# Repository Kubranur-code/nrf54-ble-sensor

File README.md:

# nRF54L10 BLE Sensor Board

A small Bluetooth Low Energy sensor board built around Nordic's nRF54L10. The chip is placed directly on the board, not used through a radio module. It runs from a single CR2032 coin cell, measures temperature, humidity and motion, and transmits through a PCB antenna I laid out myself. The board is 35 × 45 mm, has four layers and is designed in KiCad 9 for assembly at JLCPCB.

*Top side. The antenna is in the top-left corner, the nRF54L10 is in the middle and the coin-cell holder takes up the lower half. All parts are on this side.*

## Why I built this

Most hobby BLE boards use a pre-certified module. The module hides the hardest part of the design: the RF matching, the antenna and the ground around them. I wanted to do that part myself, so this board uses the bare QFN48 chip with Nordic's matching network and a printed inverted-F antenna. I added a small tuning network between them so the antenna can later be measured and adjusted with a VNA without a new board.

The second goal was low power. The board has no regulator and no power switch, and the accelerometer wakes the chip only when the board moves. A coin cell should therefore last a long time.

## Hardware overview

| | |
|---|---|
| SoC | nRF54L10-QFAA (Cortex-M33, 1 MB RRAM, 192 KB RAM, Bluetooth LE) |
| Sensors | Sensirion SHT40 (temperature/humidity), ST LIS2DH12 (accelerometer), shared I²C bus |
| Power | CR2032 straight to VDD, internal DC/DC converter, 47 µF buffer capacitor |
| Clocks | 32 MHz crystal, 32.768 kHz crystal |
| Antenna | Inverted-F PCB antenna (TI SWRA117D) after a 0 Ω + 2 × DNP π network |
| Debug | 10-pin 1.27 mm Cortex Debug connector (SWD + SWO), test pad for timing current measurements |
| User I/O | One button, one LED |
| PCB | 35 × 45 mm, 4 layers, JLC04161H-1080 stackup, ENIG, 2 × M2 mounting holes |

## Design notes

### Choosing the nRF54L10

I started with the nRF54L15, because there are already many open nRF52 designs and the nRF54L series is newer and uses less power. When I checked stock, JLCPCB had no L15, so I switched to the nRF54L10. It is pin compatible and has less memory, which this application does not need. I checked the schematic symbol pin by pin against both datasheets before changing the part.

### Running from a coin cell

The nRF54L works from 1.7 to 3.6 V, so a regulator between the cell and the chip would only add its own quiescent current. Instead, the chip's internal DC/DC converter is enabled with the 4.7 µH inductor from Nordic's reference design. A CR2032 has a high internal resistance and cannot deliver the radio's current peaks cleanly, so a 47 µF ceramic capacitor next to the holder covers them.

The LIS2DH12 stays in its low-power mode and its INT1 pin can wake the nRF54L10 from System OFF. The radio therefore only runs when something happens. Its address pin SA0 is tied to VDD, because the pin has an internal pull-up and tying it to ground would draw a small but constant current.

### Clocks

The chip can run its low-frequency clock from an internal RC oscillator, but that oscillator drifts with temperature. It has to be recalibrated regularly, which means starting the 32 MHz crystal, and its larger error forces wider BLE receive windows. Both cost more energy over time than a small 32.768 kHz crystal, so the board has one. Both crystals use the chip's internal load capacitors.

### RF path and antenna

The matching network between the ANT pin and the 50 Ω point is copied part for part from Nordic's QFAA reference layout, using the same Murata 0201 inductors and capacitors. I also kept the reference's ground return for the VSS_PA shunt capacitor: it goes back to the chip only on the top layer, not through a via. After the 50 Ω point comes a 0402 π network with a 0 Ω resistor and two unpopulated capacitor pads (C13, C14). These are the pads I will use to tune the antenna once I can measure it.

The SoC, the matching network and the antenna feed are placed on one straight line, so the RF trace from the ANT pin to the antenna has no bends. The antenna area is kept free of copper on all four layers, and a row of ground vias runs along the RF path.

### Stackup

I used JLCPCB's JLC04161H-1080 stackup. Its prepreg between the top layer and the first ground plane is only 0.076 mm thick. A thin dielectric keeps the ground close under the ANT pin, which Nordic recommends for suppressing harmonics. It also makes the 50 Ω line narrow enough for 0201 pads: as a grounded coplanar waveguide the line is 0.13 mm wide with 0.15 mm gaps.

| Layer | Use |
|---|---|
| L1 | Components, RF, most signals |
| L2 | Solid ground plane |
| L3 | VDD plane, one short signal |
| L4 | Ground pour, signals that change layer |

### Layout

The hardest part of the layout was the left side of the QFN. Its 0.4 mm pitch pins carry the button, the LED, both I²C lines, the accelerometer interrupt and the DC/DC loop. In the first placement the I²C pull-ups and the ferrite bead were directly in front of these pins, and there was no room to get the traces out. The autorouter failed here as well. Pull-ups work anywhere on the bus, so I moved them down next to the humidity sensor. The remaining traces that could not escape on the top layer change to the bottom layer through vias. The ground plane under all top-layer signals stays unbroken.

The DECRF pin needs a connection to DECA on the other side of the chip, and on the top layer that path is blocked by the crystal traces. I copied the solution from Nordic's layout: the DECRF capacitor sits right at the pin, and a via behind it carries the connection on the bottom layer to the DECA side.

The ground pours on L1 and L4 are stitched to the L2 plane with vias on a 2.5 mm grid, about λ/25 at 2.4 GHz. Two M2 mounting holes sit in opposite corners. The antenna corner has to stay free of metal and the coin-cell holder covers the fourth corner, so two diagonal holes were the practical choice. ERC and DRC, including schematic parity, finish with no violations. The reports are in `fab/`.

*Bottom side: ground pour, stitching vias and the few signals that use L4. The antenna keep-out appears top-right because the view is mirrored.*

## Project status

The design is finished, but the board has **not been manufactured yet**. Nothing in this repository has been tested on real hardware.

## Ordering from JLCPCB

1. Upload `fab/nrf54-ble-sensor-gerbers.zip`. Select 4 layers, 1.6 mm thickness, ENIG and impedance control with the JLC04161H-1080 stackup.
2. For assembly, upload `fab/nrf54-ble-sensor-bom.csv` and `fab/nrf54-ble-sensor-cpl.csv`. C13 and C14 are left out on purpose.
3. Check the part rotations in JLCPCB's placement preview before ordering. Their library sometimes uses a different orientation than KiCad, most often for QFN, LGA and crystal packages.

## Repository layout

```
nrf54-ble-sensor.kicad_*   KiCad 9 project
lib/                       symbols, footprints and 3D models not in the KiCad library
docs/                      schematic PDF and renders
fab/                       Gerbers, drill files, BOM, CPL, ERC/DRC reports
scripts/export.sh          regenerates everything in fab/ and docs/
```

All outputs are generated with `kicad-cli` by running `bash scripts/export.sh`. The 3D models of the two crystals and the SHT40 are from the LCSC/EasyEDA part library.

## References

- Nordic Semiconductor, nRF54L15/L10 product specification and QFAA reference layout v0.8
- Texas Instruments, SWRA117D, *2.4 GHz Inverted F Antenna*
- Nordic DevZone discussions on ANT pin ground distance and harmonics
- JLCPCB impedance-controlled stackups

## License

Copyright 2026 Kübranur Cici.

The hardware design files in this repository are licensed under the [CERN Open Hardware Licence Version 2 – Strongly Reciprocal](LICENSE) (CERN-OHL-S-2.0). The 3D models in `lib/parts.3dshapes` and the Nordic reference material referred to above belong to their respective owners and are not covered by this licence.

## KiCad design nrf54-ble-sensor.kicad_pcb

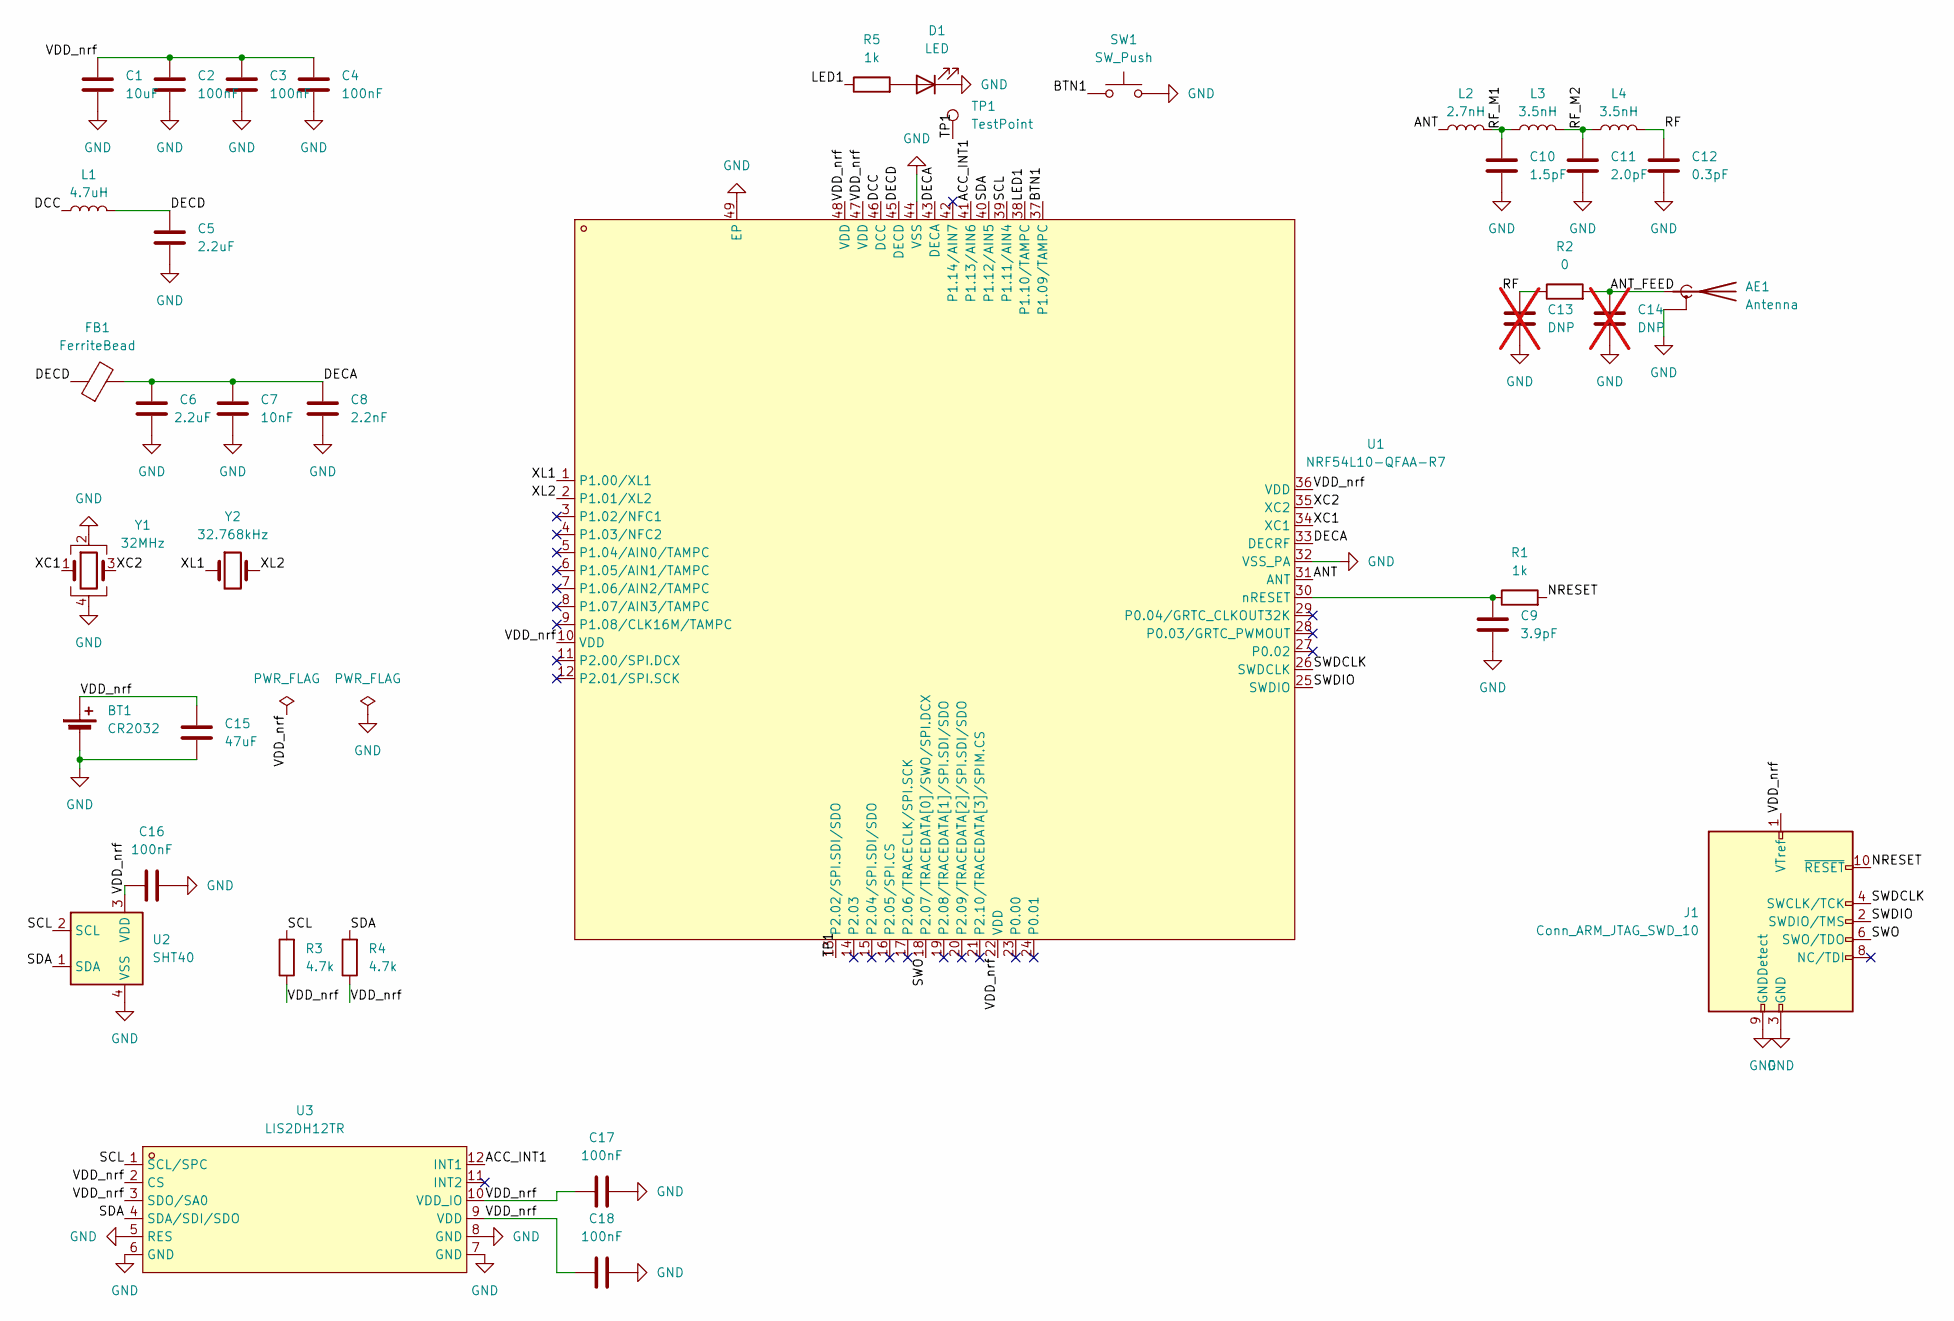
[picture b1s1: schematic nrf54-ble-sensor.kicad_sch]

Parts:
AE1: Antenna; Texas_SWRA117D_2.4GHz_Left
BT1: CR2032; BatteryHolder_Keystone_3034_1x20mm; LCSC Part C5199422
C1: 10uF; C_0402_1005Metric; LCSC Part C15525
C2, C3, C4, C16, C17, C18: 100nF; C_0402_1005Metric; LCSC Part C1525
C5, C6: 2.2uF; C_0402_1005Metric; LCSC Part C12530
C7: 10nF; C_0402_1005Metric; LCSC Part C15195
C8: 2.2nF; C_0201_0603Metric; LCSC Part C161488
C9: 3.9pF; C_0402_1005Metric; LCSC Part C1566
C10: 1.5pF; C_0201_0603Metric; LCSC Part C435397
C11: 2.0pF; C_0201_0603Metric; LCSC Part C668326
C12: 0.3pF; C_0201_0603Metric; LCSC Part C237273
C13, C14: DNP; C_0402_1005Metric; not fitted
C15: 47uF; C_0805_2012Metric; LCSC Part C16780
D1: LED; LED_0603_1608Metric; LCSC Part C2286
FB1: FerriteBead; L_0402_1005Metric; LCSC Part C337873
J1: Conn_ARM_JTAG_SWD_10; PinHeader_2x05_P1.27mm_Vertical_SMD; LCSC Part C41376037
L1: 4.7uH; L_0603_1608Metric; LCSC Part C295681
L2: 2.7nH; L_0201_0603Metric; LCSC Part C7216765
L3, L4: 3.5nH; L_0201_0603Metric; LCSC Part C3911055
R1, R5: 1k; R_0402_1005Metric; LCSC Part C11702
R2: 0; R_0402_1005Metric; LCSC Part C17168
R3, R4: 4.7k; R_0402_1005Metric; LCSC Part C25900
SW1: SW_Push; SW_SPST_B3U-1000P; LCSC Part C231329
TP1: TestPoint; TestPoint_Pad_D1.0mm
U1: NRF54L10-QFAA-R7; QFN-48_L6.0-W6.0-P0.40-TL-EP4.6; MPN NRF54L15-QFAA-R; LCSC Part C44800139
U2: SHT40; Sensirion_DFN-4_1.5x1.5mm_P0.8mm_SHT4x_NoCentralPad; LCSC Part C2909890
U3: LIS2DH12TR; LGA-12_L2.0-W2.0-P0.50-BL; MPN LIS2DH12TR; LCSC Part C110926
Y1: 32MHz; Crystal_SMD_2016-4Pin_2.0x1.6mm; LCSC Part C5339095
Y2: 32.768kHz; Crystal_SMD_2012-2Pin_2.0x1.2mm; LCSC Part C96341

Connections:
/ACC_INT1: U1.41 (P1.13/AIN6), U3.12 (INT1)
/ANT: L2.1, U1.31 (ANT)
/ANT_FEED: AE1.1 (A), C14.1, R2.2
/BTN1: SW1.1, U1.37 (P1.09/TAMPC)
/DCC: L1.1, U1.46 (DCC)
/DECA: C6.1, C7.1, C8.1, FB1.2, U1.33 (DECRF), U1.43 (DECA)
/DECD: C5.1, FB1.1, L1.2, U1.45 (DECD)
/LED1: R5.1, U1.38 (P1.10/TAMPC)
/NRESET: J1.10 (~RESET), R1.2
/RF: C12.1, C13.1, L4.2, R2.1
/RF_M1: C10.1, L2.2, L3.1
/RF_M2: C11.1, L3.2, L4.1
/SCL: R3.2, U1.39 (P1.11/AIN4), U2.2 (SCL), U3.1 (SCL/SPC)
/SDA: R4.2, U1.40 (P1.12/AIN5), U2.1 (SDA), U3.4 (SDA/SDI/SDO)
/SWDCLK: J1.4 (SWCLK/TCK), U1.26 (SWDCLK)
/SWDIO: J1.2 (SWDIO/TMS), U1.25 (SWDIO)
/SWO: J1.6 (SWO/TDO), U1.18 (P2.07/TRACEDATA[0]/SWO/SPI.DCX)
/TP1: TP1.1, U1.13 (P2.02/SPI.SDI/SDO)
/VDD_nrf: BT1.1 (+), C1.1, C2.1, C3.1, C4.1, C15.1, C16.1, C17.1, C18.1, J1.1 (VTref), R3.1, R4.1, U1.10 (VDD), U1.22 (VDD), U1.36 (VDD), U1.47 (VDD), U1.48 (VDD), U2.3 (VDD), U3.2 (CS), U3.3 (SDO/SA0), U3.9 (VDD), U3.10 (VDD_IO)
/XC1: U1.34 (XC1), Y1.1
/XC2: U1.35 (XC2), Y1.3
/XL1: U1.1 (P1.00/XL1), Y2.1
/XL2: U1.2 (P1.01/XL2), Y2.2
GND: AE1.2 (Shield), BT1.2 (-), C1.2, C2.2, C3.2, C4.2, C5.2, C6.2, C7.2, C8.2, C9.2, C10.2, C11.2, C12.2, C13.2, C14.2, C15.2, C16.2, C17.2, C18.2, D1.1 (K), J1.3 (GND), J1.5 (GND), J1.9 (GNDDetect), SW1.2, U1.32 (VSS_PA), U1.44 (VSS), U1.49 (EP), U2.4 (VSS), U3.5 (RES), U3.6 (GND), U3.7 (GND), U3.8 (GND), Y1.2, Y1.4
unnamed: D1.2 (A), R5.2
unnamed: C9.1, R1.1, U1.30 (nRESET)

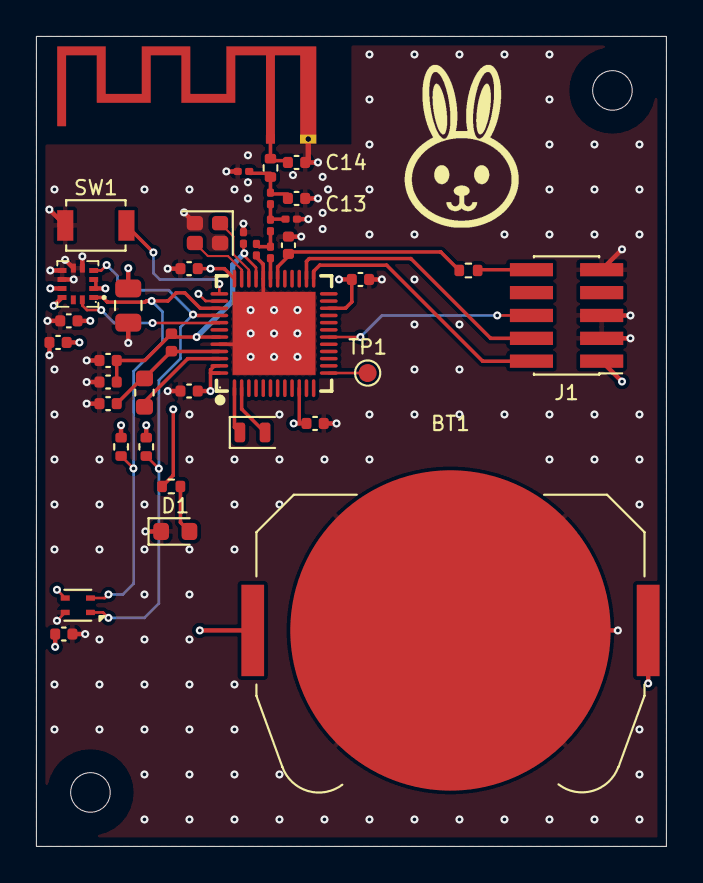
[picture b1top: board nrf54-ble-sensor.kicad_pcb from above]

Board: 4 copper layers, 35.0 x 45.0 mm, 41 parts (0 on the bottom side), 26 nets.

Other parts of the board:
H1, H2: MountingHole_2.2mm_M2

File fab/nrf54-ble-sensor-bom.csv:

"Designator","Comment","Footprint","Quantity","LCSC Part #"
"BT1","CR2032","Battery:BatteryHolder_Keystone_3034_1x20mm","1","C5199422"
"C1","10uF","Capacitor_SMD:C_0402_1005Metric","1","C15525"
"C2,C3,C4,C16,C17,C18","100nF","Capacitor_SMD:C_0402_1005Metric","6","C1525"
"C5,C6","2.2uF","Capacitor_SMD:C_0402_1005Metric","2","C12530"
"C7","10nF","Capacitor_SMD:C_0402_1005Metric","1","C15195"
"C8","2.2nF","Capacitor_SMD:C_0201_0603Metric","1","C161488"
"C9","3.9pF","Capacitor_SMD:C_0402_1005Metric","1","C1566"
"C10","1.5pF","Capacitor_SMD:C_0201_0603Metric","1","C435397"
"C11","2.0pF","Capacitor_SMD:C_0201_0603Metric","1","C668326"
"C12","0.3pF","Capacitor_SMD:C_0201_0603Metric","1","C237273"
"C15","47uF","Capacitor_SMD:C_0805_2012Metric","1","C16780"
"D1","LED","LED_SMD:LED_0603_1608Metric","1","C2286"
"FB1","FerriteBead","Inductor_SMD:L_0402_1005Metric","1","C337873"
"J1","Conn_ARM_JTAG_SWD_10","Connector_PinHeader_1.27mm:PinHeader_2x05_P1.27mm_Vertical_SMD","1","C41376037"
"L1","4.7uH","Inductor_SMD:L_0603_1608Metric","1","C295681"
"L2","2.7nH","Inductor_SMD:L_0201_0603Metric","1","C7216765"
"L3,L4","3.5nH","Inductor_SMD:L_0201_0603Metric","2","C3911055"
"R1,R5","1k","Resistor_SMD:R_0402_1005Metric","2","C11702"
"R2","0","Resistor_SMD:R_0402_1005Metric","1","C17168"
"R3,R4","4.7k","Resistor_SMD:R_0402_1005Metric","2","C25900"
"SW1","SW_Push","Button_Switch_SMD:SW_SPST_B3U-1000P","1","C231329"
"U1","NRF54L10-QFAA-R7","nrf54:QFN-48_L6.0-W6.0-P0.40-TL-EP4.6","1","C44800139"
"U2","SHT40","Sensor_Humidity:Sensirion_DFN-4_1.5x1.5mm_P0.8mm_SHT4x_NoCentralPad","1","C2909890"
"U3","LIS2DH12TR","sensors:LGA-12_L2.0-W2.0-P0.50-BL","1","C110926"
"Y1","32MHz","Crystal:Crystal_SMD_2016-4Pin_2.0x1.6mm","1","C5339095"
"Y2","32.768kHz","Crystal:Crystal_SMD_2012-2Pin_2.0x1.2mm","1","C96341"
